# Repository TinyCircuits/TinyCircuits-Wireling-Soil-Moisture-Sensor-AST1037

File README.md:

# TinyCircuits Wireling Soil Moisture Sensor
# AST1037 Rev1

The design files are located under design_files/ for the TinyCircuits AST1037 Rev 1 PCB. This is a Wireling board which etects moisture in soil using the ATTiny25 and this plant tag shaped Whisker so you never have to guess when to water!

Format is in Cadsoft Eagle format - Eagle version 6.2 was used for the original design.

For more infomation on this, check out the product page at TinyCircuits.com

# License:

Design by TinyCircuits.
All design files are released under the Creative Commons Attribution Share-Alike 3.0 License, see the following link for details: http://creativecommons.org/licenses/by-sa/3.0

All text above must be included in any redistribution or derived design

This project uses designs and concepts developed as part of the Arduino project and the LilyPad project.  The TinyCircuits design files themselves (schematics, PCB and libraries) are not directly derived from these works' design files and have been created new, however the concepts and basic architecture behind the TinyDuino and TinyLily products are derived and we thank the hard work of the organizations below for their contributions to open-source hardware:
  
Original Arduino Uno Design by Team Arduino

LilyPad Arduino Design by Leah Buechley and Sparkfun Electronics

Please support the open-source hardware community

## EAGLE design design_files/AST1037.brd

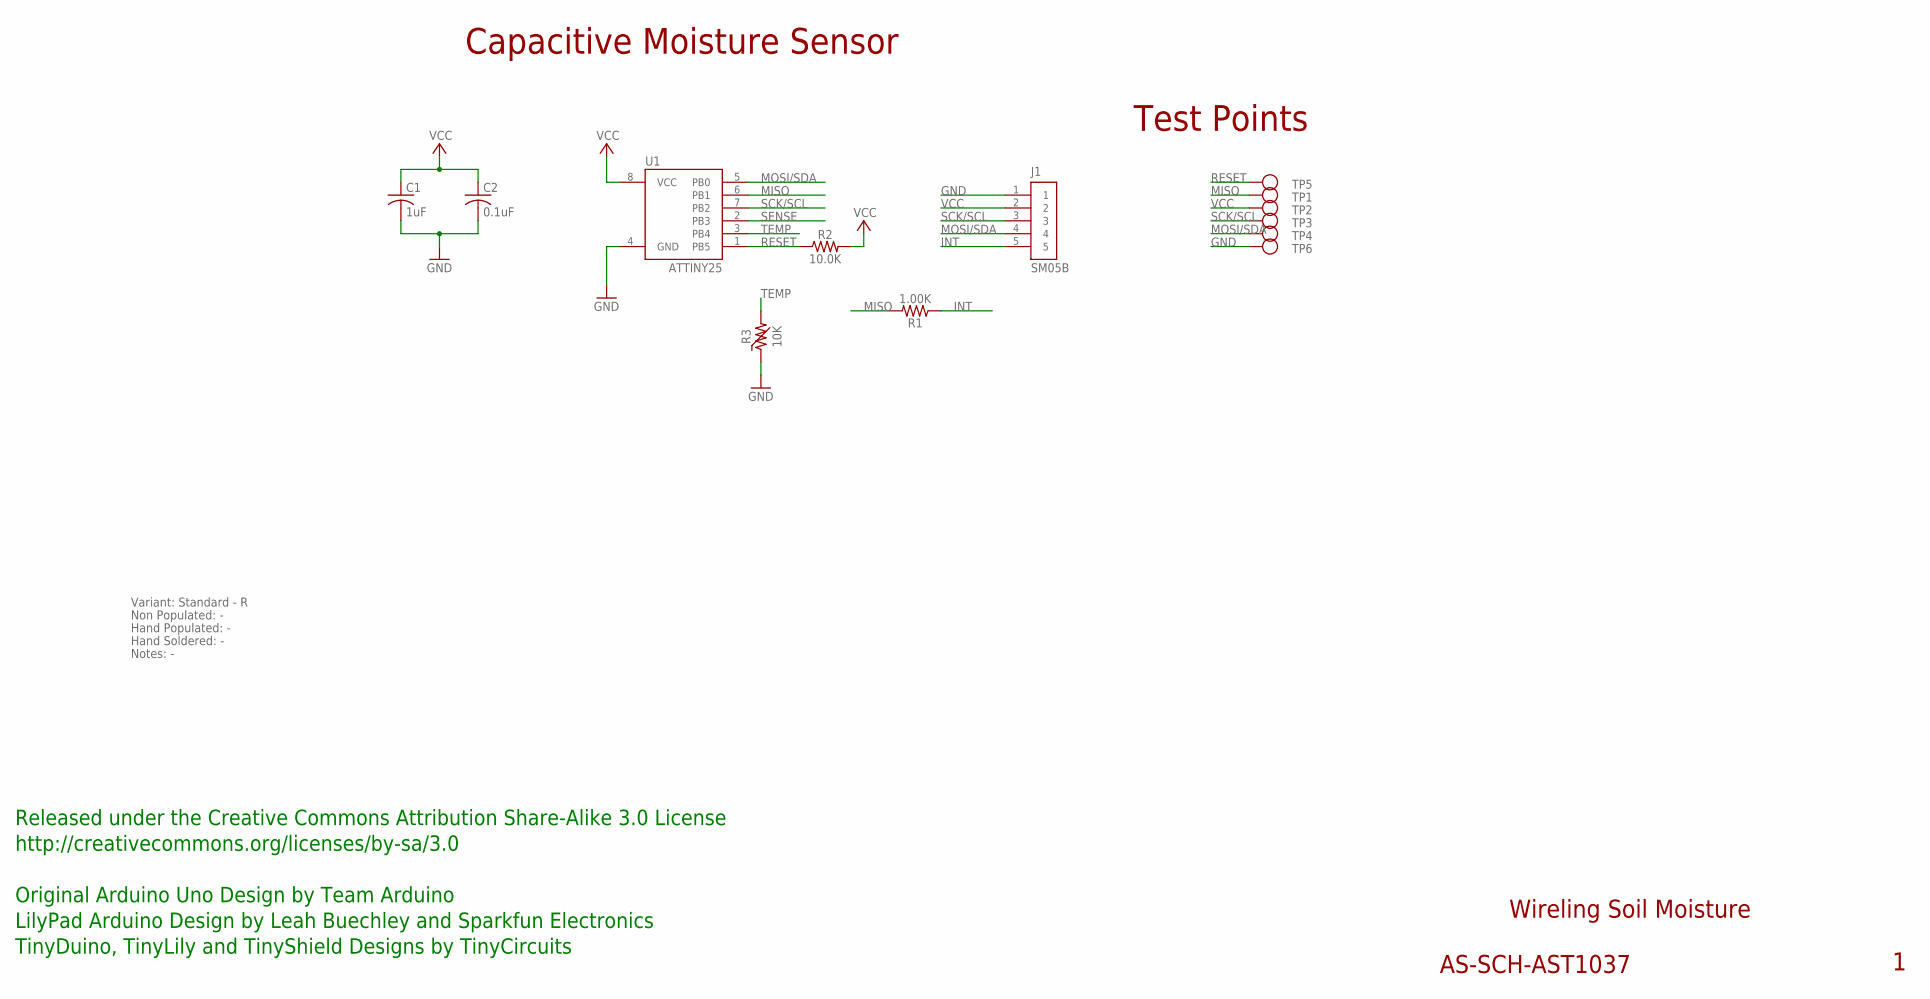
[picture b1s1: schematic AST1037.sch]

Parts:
C1: 1uF; C0603; PARTNO AS-ITM-00410
C2: 0.1uF; C0402
J1: SM05B; JST_SH_5X1
R1: 1.00K; 0402; PARTNO AS-ITM-00003
R2: 10.0K; 0402
R3: 10K; 0402
TP1, TP2, TP3, TP4, TP5, TP6: TEST_POINT; TEST_POINT_1MM
U1: ATTINY25; SO-08-COMPACT

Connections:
GND: C1.2, C2.2, J1.1, R3.1, TP6.P$1, U1.4 (GND)
INT: J1.5, R1.1
MISO: R1.2, TP1.P$1, U1.6 (PB1)
MOSI/SDA: J1.4, TP4.P$1, U1.5 (PB0)
RESET: R2.1, TP5.P$1, U1.1 (PB5)
SCK/SCL: J1.3, TP3.P$1, U1.7 (PB2)
SENSE: U1.2 (PB3)
TEMP: R3.2, U1.3 (PB4)
VCC: C1.1, C2.1, J1.2, R2.2, TP2.P$1, U1.8 (VCC)

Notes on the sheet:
Wireling Soil Moisture
AS-SCH-AST1037
Capacitive Moisture Sensor
Released under the Creative Commons Attribution Share-Alike 3.0 License
http://creativecommons.org/licenses/by-sa/3.0
Original Arduino Uno Design by Team Arduino
TinyDuino, TinyLily and TinyShield Designs by TinyCircuits
LilyPad Arduino Design by Leah Buechley and Sparkfun Electronics
Test Points
Non Populated: -
Hand Populated: -
Hand Soldered: -
Variant: Standard - R
Notes: -

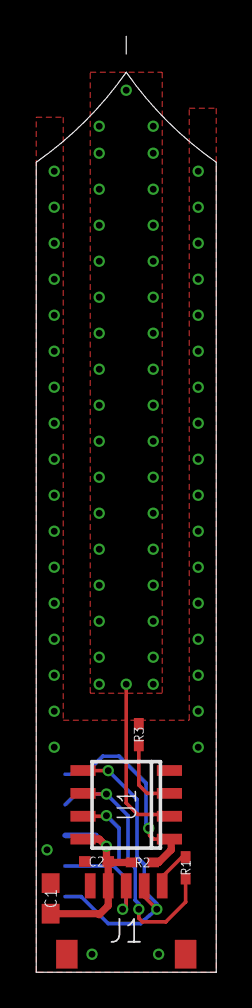
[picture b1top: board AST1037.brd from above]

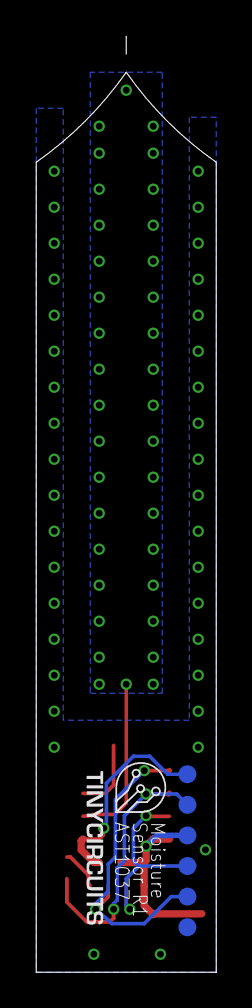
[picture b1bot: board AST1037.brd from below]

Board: 2 copper layers, 10.0 x 52.0 mm, 14 parts (6 on the bottom side), 8 nets.

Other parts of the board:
U$1: DOCFIELD-TINYCIRCUITS-PCB

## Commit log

2019-08-05 added datasheet
2019-12-17 updated documentation
2019-12-26 new example code
2019-12-26 added image
2020-01-09 added images and examples
2020-01-09 fixed naming issue
2020-01-14 moist pictures
2020-01-14 these variable labels were just WRONG
2020-02-04 mass image update
2020-08-14 Add CAD data
2021-01-05 ATtiny25 library update
2022-01-24 add updated example
